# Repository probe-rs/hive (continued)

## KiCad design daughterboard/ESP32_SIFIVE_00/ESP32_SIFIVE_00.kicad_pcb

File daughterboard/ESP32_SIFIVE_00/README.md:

## Daughterboard ESP32_SIFIVE_00
This board features RISC-V and Xtensa cores.

### Targets
The following targets are implemented on this Daughterboard:
| Designation | MCU |
| --- | --- |
| target0 | ESP32-S3-WROOM-1-N8R8 |
| target1 | ESP32-S2 |
| target2 | LOFIVE-R1 (FE310-G002) |
| target3 | ESP32-C3 |

### Partlist
The partlist for this Daughterboard is available [here](https://octopart.com/bom-tool/JTwGMmL3).

### Other
The target3 and target1 devices have separate flash memory, as the currently available cores do not have any embedded flash.

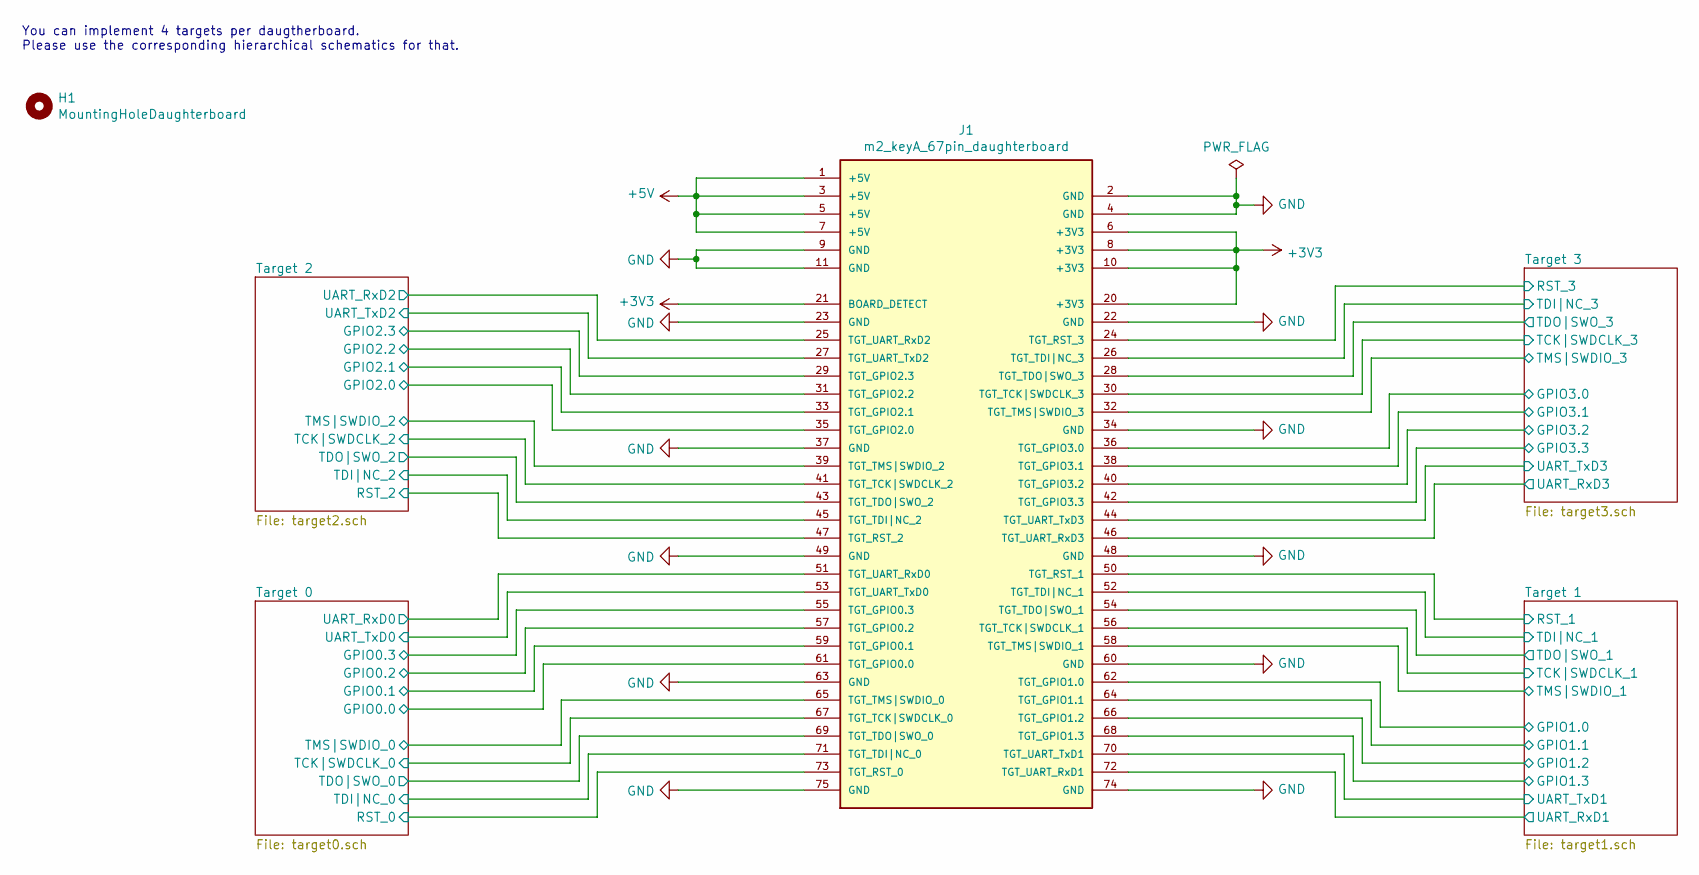
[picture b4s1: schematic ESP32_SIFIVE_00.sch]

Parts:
H1: MountingHoleDaughterboard; MountingHole_2.7mm_M2.5
J1: m2_keyA_67pin_daughterboard; m2_keyB

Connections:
+3V3: J1.6 (+3V3), J1.8 (+3V3), J1.10 (+3V3), J1.20 (+3V3), J1.21 (BOARD_DETECT); also elsewhere on the board
+5V: J1.1 (+5V), J1.3 (+5V), J1.5 (+5V), J1.7 (+5V); also elsewhere on the board
/Target 0/GPIO0.0: J1.61 (TGT_GPIO0.0); also elsewhere on the board
/Target 0/GPIO0.1: J1.59 (TGT_GPIO0.1); also elsewhere on the board
/Target 0/GPIO0.2: J1.57 (TGT_GPIO0.2); also elsewhere on the board
/Target 0/GPIO0.3: J1.55 (TGT_GPIO0.3); also elsewhere on the board
/Target 0/RST_0: J1.73 (TGT_RST_0); also elsewhere on the board
/Target 0/TCK|SWDCLK_0: J1.67 (TGT_TCK|SWDCLK_0); also elsewhere on the board
/Target 0/TDI|NC_0: J1.71 (TGT_TDI|NC_0); also elsewhere on the board
/Target 0/TDO|SWO_0: J1.69 (TGT_TDO|SWO_0); also elsewhere on the board
/Target 0/TMS|SWDIO_0: J1.65 (TGT_TMS|SWDIO_0); also elsewhere on the board
/Target 0/UART_RxD0: J1.51 (TGT_UART_RxD0); also elsewhere on the board
/Target 0/UART_TxD0: J1.53 (TGT_UART_TxD0); also elsewhere on the board
/Target 1/GPIO1.0: J1.62 (TGT_GPIO1.0); also elsewhere on the board
/Target 1/GPIO1.1: J1.64 (TGT_GPIO1.1); also elsewhere on the board
/Target 1/GPIO1.2: J1.66 (TGT_GPIO1.2); also elsewhere on the board
/Target 1/GPIO1.3: J1.68 (TGT_GPIO1.3); also elsewhere on the board
/Target 1/RST_1: J1.50 (TGT_RST_1); also elsewhere on the board
/Target 1/TCK|SWDCLK_1: J1.56 (TGT_TCK|SWDCLK_1); also elsewhere on the board
/Target 1/TDI|NC_1: J1.52 (TGT_TDI|NC_1); also elsewhere on the board
/Target 1/TDO|SWO_1: J1.54 (TGT_TDO|SWO_1); also elsewhere on the board
/Target 1/TMS|SWDIO_1: J1.58 (TGT_TMS|SWDIO_1); also elsewhere on the board
/Target 1/UART_RxD1: J1.72 (TGT_UART_RxD1); also elsewhere on the board
/Target 1/UART_TxD1: J1.70 (TGT_UART_TxD1); also elsewhere on the board
/Target 2/GPIO2.0: J1.35 (TGT_GPIO2.0); also elsewhere on the board
/Target 2/GPIO2.1: J1.33 (TGT_GPIO2.1); also elsewhere on the board
/Target 2/GPIO2.2: J1.31 (TGT_GPIO2.2); also elsewhere on the board
/Target 2/GPIO2.3: J1.29 (TGT_GPIO2.3); also elsewhere on the board
/Target 2/RST_2: J1.47 (TGT_RST_2); also elsewhere on the board
/Target 2/TCK|SWDCLK_2: J1.41 (TGT_TCK|SWDCLK_2); also elsewhere on the board
/Target 2/TDI|NC_2: J1.45 (TGT_TDI|NC_2); also elsewhere on the board
/Target 2/TDO|SWO_2: J1.43 (TGT_TDO|SWO_2); also elsewhere on the board
/Target 2/TMS|SWDIO_2: J1.39 (TGT_TMS|SWDIO_2); also elsewhere on the board
/Target 2/UART_RxD2: J1.25 (TGT_UART_RxD2); also elsewhere on the board
/Target 2/UART_TxD2: J1.27 (TGT_UART_TxD2); also elsewhere on the board
/Target 3/GPIO3.0: J1.36 (TGT_GPIO3.0); also elsewhere on the board
/Target 3/GPIO3.1: J1.38 (TGT_GPIO3.1); also elsewhere on the board
/Target 3/GPIO3.2: J1.40 (TGT_GPIO3.2); also elsewhere on the board
/Target 3/GPIO3.3: J1.42 (TGT_GPIO3.3); also elsewhere on the board
/Target 3/RST_3: J1.24 (TGT_RST_3); also elsewhere on the board
/Target 3/TCK|SWDCLK_3: J1.30 (TGT_TCK|SWDCLK_3); also elsewhere on the board
/Target 3/TDI|NC_3: J1.26 (TGT_TDI|NC_3); also elsewhere on the board
/Target 3/TDO|SWO_3: J1.28 (TGT_TDO|SWO_3); also elsewhere on the board
/Target 3/TMS|SWDIO_3: J1.32 (TGT_TMS|SWDIO_3); also elsewhere on the board
/Target 3/UART_RxD3: J1.46 (TGT_UART_RxD3); also elsewhere on the board
/Target 3/UART_TxD3: J1.44 (TGT_UART_TxD3); also elsewhere on the board
GND: J1.2 (GND), J1.4 (GND), J1.9 (GND), J1.11 (GND), J1.22 (GND), J1.23 (GND), J1.34 (GND), J1.37 (GND), J1.48 (GND), J1.49 (GND), J1.60 (GND), J1.63 (GND), J1.74 (GND), J1.75 (GND); also elsewhere on the board

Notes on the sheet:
You can implement 4 targets per daugtherboard. Please use the corresponding hierarchical schematics for that.

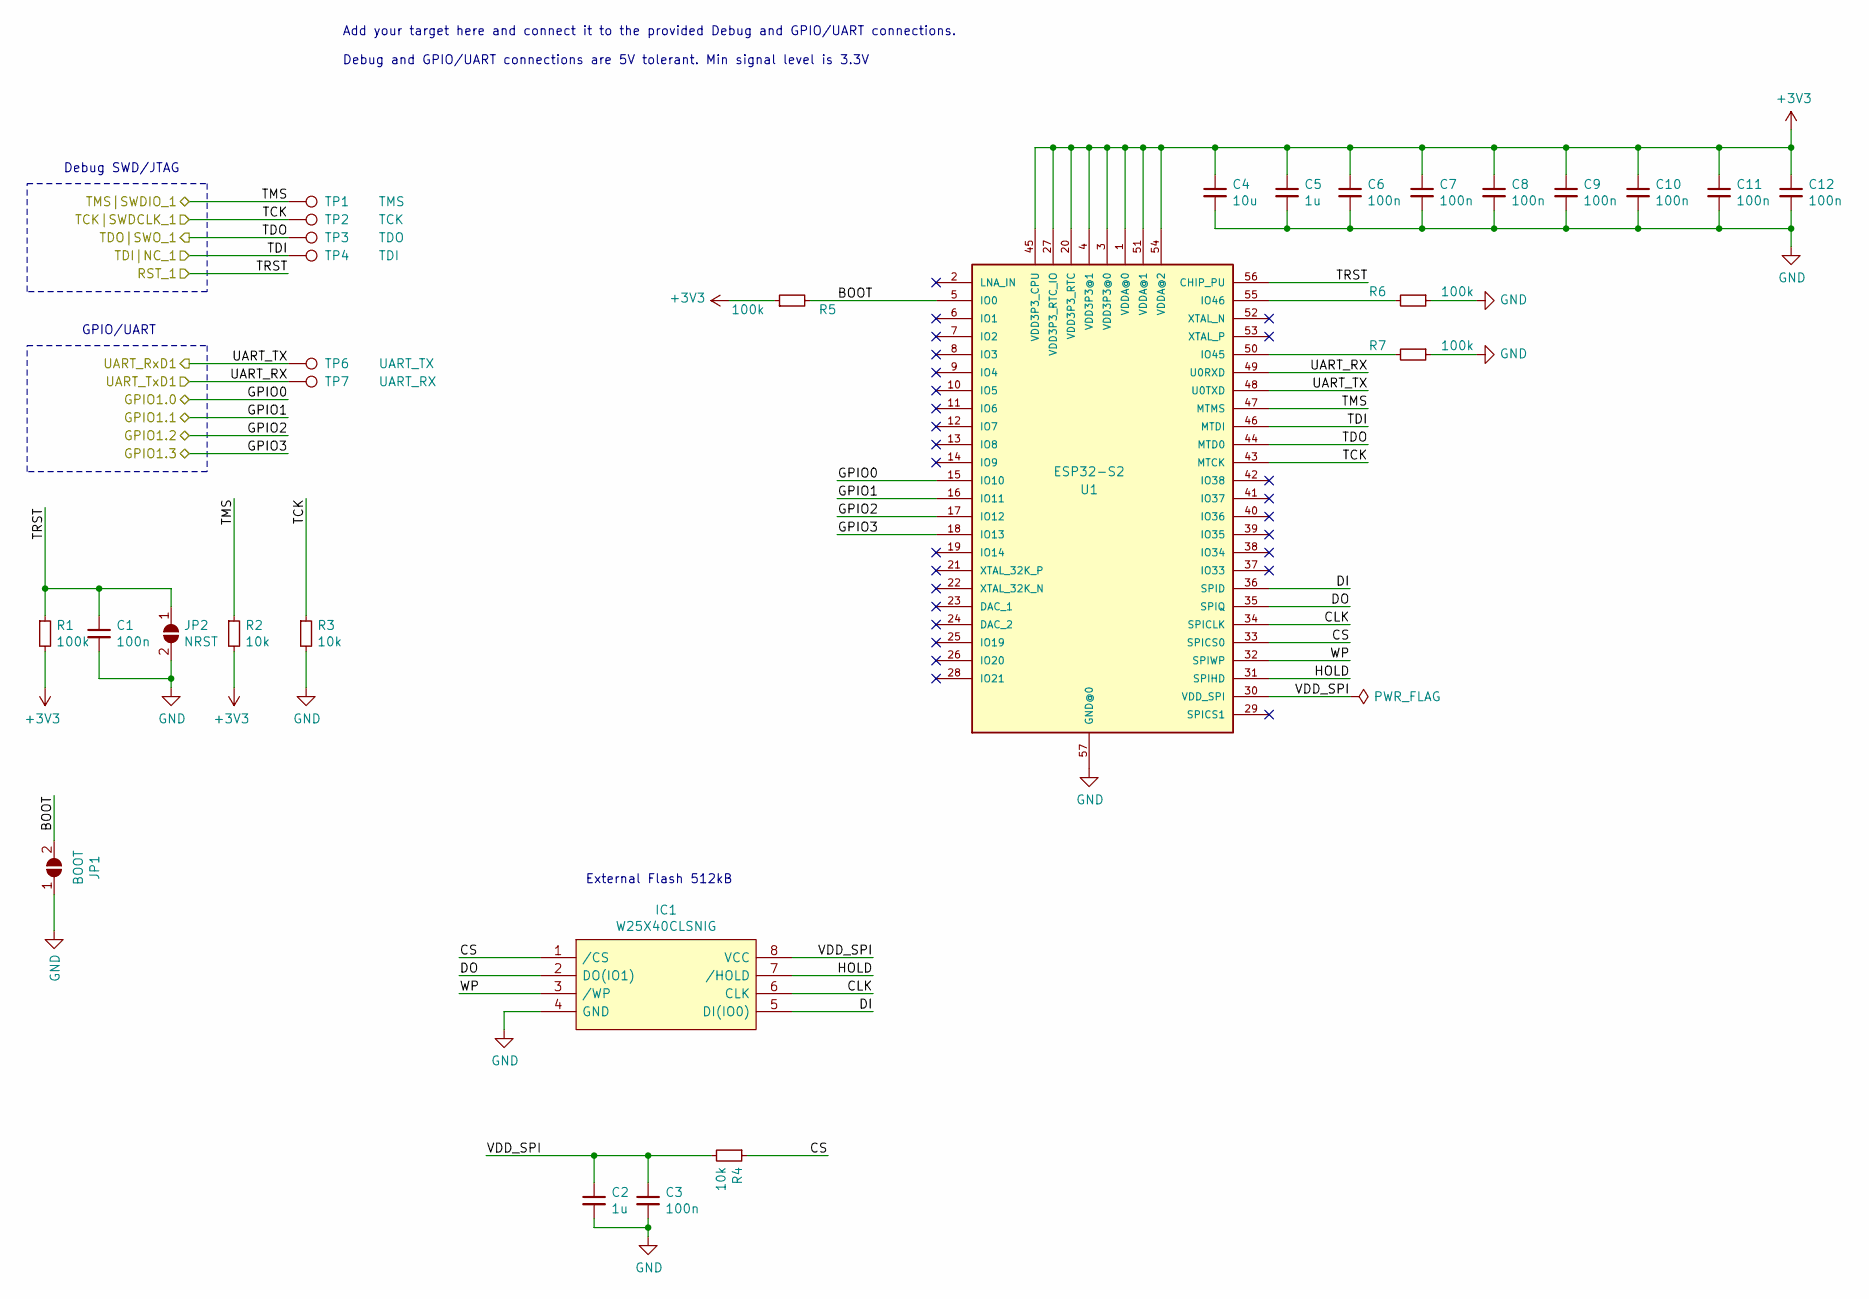
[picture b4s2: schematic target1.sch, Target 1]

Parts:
C1, C3, C6, C7, C8, C9, C10, C11, C12: 100n; C_0603_1608Metric_Pad1.05x0.95mm_HandSolder
C2, C5: 1u; C_0603_1608Metric_Pad1.05x0.95mm_HandSolder
C4: 10u; C_0603_1608Metric_Pad1.05x0.95mm_HandSolder
IC1: W25X40CLSNIG; Mouser Part Number 454-W25X40CLSNIG
JP1: BOOT; SolderJumper-2_P1.3mm_Open_TrianglePad1.0x1.5mm
JP2: NRST; SolderJumper-2_P1.3mm_Open_TrianglePad1.0x1.5mm
R1, R5, R6, R7: 100k; R_0603_1608Metric_Pad1.05x0.95mm_HandSolder
R2, R3, R4: 10k; R_0603_1608Metric_Pad1.05x0.95mm_HandSolder
TP1: TMS; TestPoint_Pad_1.0x1.0mm
TP2: TCK; TestPoint_Pad_1.0x1.0mm
TP3: TDO; TestPoint_Pad_1.0x1.0mm
TP4: TDI; TestPoint_Pad_1.0x1.0mm
TP6: UART_TX; TestPoint_Pad_1.0x1.0mm
TP7: UART_RX; TestPoint_Pad_1.0x1.0mm
U1: ESP32-S2; MANUFACTURER_PART_NUMBE ESP32-S2

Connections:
+3V3: C4.1, C5.1, C6.1, C7.1, C8.1, C9.1, C10.1, C11.1, C12.1, R1.2, R2.2, R5.1, U1.1 (VDDA@0), U1.3 (VDD3P3@0), U1.4 (VDD3P3@1), U1.20 (VDD3P3_RTC), U1.27 (VDD3P3_RTC_IO), U1.45 (VDD3P3_CPU), U1.51 (VDDA@1), U1.54 (VDDA@2); also elsewhere on the board
/Target 1/BOOT: JP1.2 (B), R5.2, U1.5 (IO0)
/Target 1/CLK: IC1.6 (CLK), U1.34 (SPICLK)
/Target 1/CS: IC1.1 (/CS), R4.1, U1.33 (SPICS0)
/Target 1/DI: IC1.5 (DI(IO0)), U1.36 (SPID)
/Target 1/DO: IC1.2 (DO(IO1)), U1.35 (SPIQ)
/Target 1/GPIO1.0: U1.15 (IO10); also elsewhere on the board
/Target 1/GPIO1.1: U1.16 (IO11); also elsewhere on the board
/Target 1/GPIO1.2: U1.17 (IO12); also elsewhere on the board
/Target 1/GPIO1.3: U1.18 (IO13); also elsewhere on the board
/Target 1/HOLD: IC1.7 (/HOLD), U1.31 (SPIHD)
/Target 1/RST_1: C1.1, JP2.1 (A), R1.1, U1.56 (CHIP_PU); also elsewhere on the board
/Target 1/TCK|SWDCLK_1: R3.1, TP2.1, U1.43 (MTCK); also elsewhere on the board
/Target 1/TDI|NC_1: TP4.1, U1.46 (MTDI); also elsewhere on the board
/Target 1/TDO|SWO_1: TP3.1, U1.44 (MTD0); also elsewhere on the board
/Target 1/TMS|SWDIO_1: R2.1, TP1.1, U1.47 (MTMS); also elsewhere on the board
/Target 1/UART_RxD1: TP6.1, U1.48 (U0TXD); also elsewhere on the board
/Target 1/UART_TxD1: TP7.1, U1.49 (U0RXD); also elsewhere on the board
/Target 1/VDD_SPI: C2.1, C3.1, IC1.8 (VCC), R4.2, U1.30 (VDD_SPI)
/Target 1/WP: IC1.3 (/WP), U1.32 (SPIWP)
GND: C1.2, C2.2, C3.2, C4.2, C5.2, C6.2, C7.2, C8.2, C9.2, C10.2, C11.2, C12.2, IC1.4 (GND), JP1.1 (A), JP2.2 (B), R3.2, R6.1, R7.1, U1.57 (GND@0); also elsewhere on the board
unnamed: R6.2, U1.55 (IO46)
unnamed: R7.2, U1.50 (IO45)

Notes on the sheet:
Debug SWD/JTAG
GPIO/UART
Add your target here and connect it to the provided Debug and GPIO/UART connections. Debug and GPIO/UART connections are 5V tolerant. Min signal level is 3.3V
External Flash 512kB

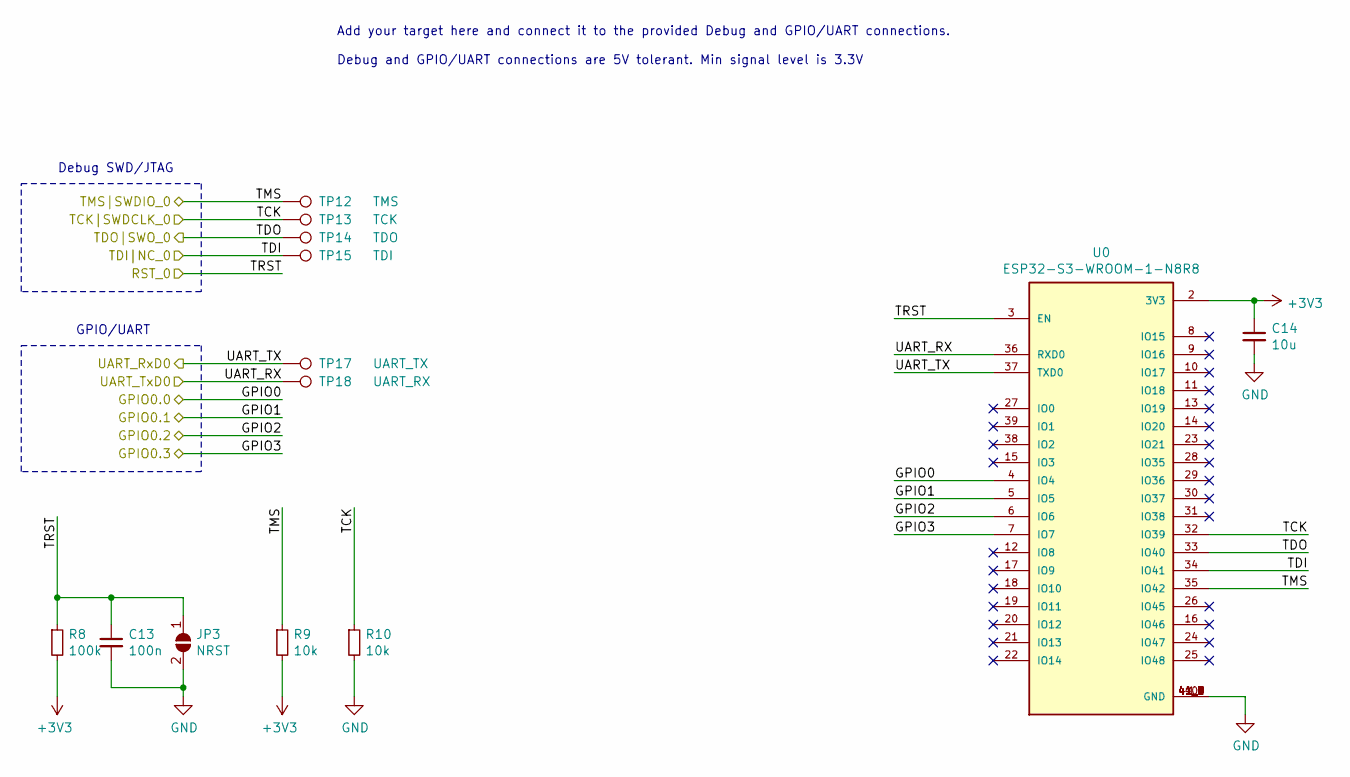
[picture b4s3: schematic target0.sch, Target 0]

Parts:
C13: 100n; C_0603_1608Metric_Pad1.05x0.95mm_HandSolder
C14: 10u; C_0603_1608Metric_Pad1.05x0.95mm_HandSolder
JP3: NRST; SolderJumper-2_P1.3mm_Open_TrianglePad1.0x1.5mm
R8: 100k; R_0603_1608Metric_Pad1.05x0.95mm_HandSolder
R9, R10: 10k; R_0603_1608Metric_Pad1.05x0.95mm_HandSolder
TP12: TMS; TestPoint_Pad_1.0x1.0mm
TP13: TCK; TestPoint_Pad_1.0x1.0mm
TP14: TDO; TestPoint_Pad_1.0x1.0mm
TP15: TDI; TestPoint_Pad_1.0x1.0mm
TP17: UART_TX; TestPoint_Pad_1.0x1.0mm
TP18: UART_RX; TestPoint_Pad_1.0x1.0mm
U0: ESP32-S3-WROOM-1-N8R8; XCVR_ESP32-S3-WROOM-1-N8R8; PARTREV v0.6

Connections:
+3V3: C14.1, R8.2, R9.2, U0.2 (3V3); also elsewhere on the board
/Target 0/GPIO0.0: U0.4 (IO4); also elsewhere on the board
/Target 0/GPIO0.1: U0.5 (IO5); also elsewhere on the board
/Target 0/GPIO0.2: U0.6 (IO6); also elsewhere on the board
/Target 0/GPIO0.3: U0.7 (IO7); also elsewhere on the board
/Target 0/RST_0: C13.1, JP3.1 (A), R8.1, U0.3 (EN); also elsewhere on the board
/Target 0/TCK|SWDCLK_0: R10.1, TP13.1, U0.32 (IO39); also elsewhere on the board
/Target 0/TDI|NC_0: TP15.1, U0.34 (IO41); also elsewhere on the board
/Target 0/TDO|SWO_0: TP14.1, U0.33 (IO40); also elsewhere on the board
/Target 0/TMS|SWDIO_0: R9.1, TP12.1, U0.35 (IO42); also elsewhere on the board
/Target 0/UART_RxD0: TP17.1, U0.37 (TXD0); also elsewhere on the board
/Target 0/UART_TxD0: TP18.1, U0.36 (RXD0); also elsewhere on the board
GND: C13.2, C14.2, JP3.2 (B), R10.2, U0.1 (GND), U0.40 (GND), U0.41_1 (GND), U0.41_2 (GND), U0.41_3 (GND), U0.41_4 (GND), U0.41_5 (GND), U0.41_6 (GND), U0.41_7 (GND), U0.41_8 (GND), U0.41_9 (GND); also elsewhere on the board

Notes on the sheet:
Debug SWD/JTAG
GPIO/UART
Add your target here and connect it to the provided Debug and GPIO/UART connections. Debug and GPIO/UART connections are 5V tolerant. Min signal level is 3.3V

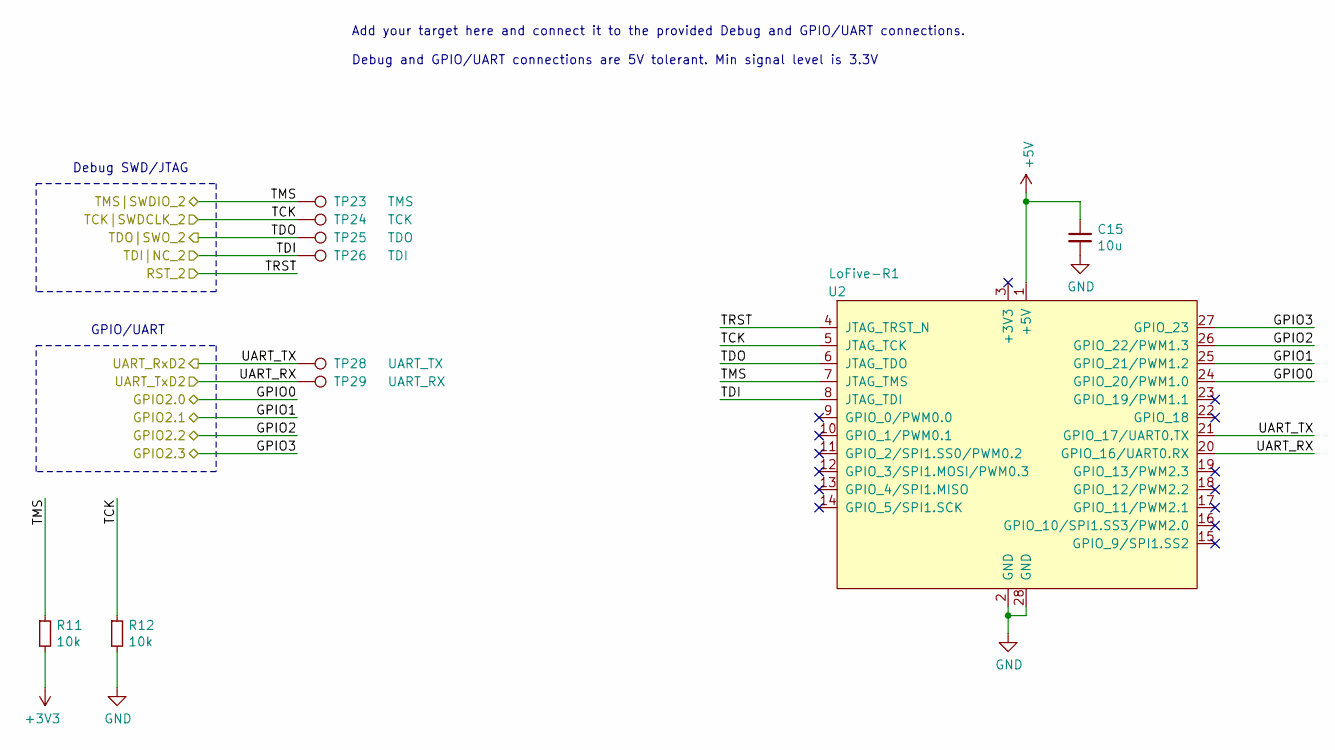
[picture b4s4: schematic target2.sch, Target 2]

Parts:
C15: 10u; C_0603_1608Metric_Pad1.05x0.95mm_HandSolder
R11, R12: 10k; R_0603_1608Metric_Pad1.05x0.95mm_HandSolder
TP23: TMS; TestPoint_Pad_1.0x1.0mm
TP24: TCK; TestPoint_Pad_1.0x1.0mm
TP25: TDO; TestPoint_Pad_1.0x1.0mm
TP26: TDI; TestPoint_Pad_1.0x1.0mm
TP28: UART_TX; TestPoint_Pad_1.0x1.0mm
TP29: UART_RX; TestPoint_Pad_1.0x1.0mm
U2: LoFive-R1

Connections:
+3V3: R11.2; also elsewhere on the board
+5V: C15.1, U2.1 (+5V); also elsewhere on the board
/Target 2/GPIO2.0: U2.24 (GPIO_20/PWM1.0); also elsewhere on the board
/Target 2/GPIO2.1: U2.25 (GPIO_21/PWM1.2); also elsewhere on the board
/Target 2/GPIO2.2: U2.26 (GPIO_22/PWM1.3); also elsewhere on the board
/Target 2/GPIO2.3: U2.27 (GPIO_23); also elsewhere on the board
/Target 2/RST_2: U2.4 (JTAG_TRST_N); also elsewhere on the board
/Target 2/TCK|SWDCLK_2: R12.1, TP24.1, U2.5 (JTAG_TCK); also elsewhere on the board
/Target 2/TDI|NC_2: TP26.1, U2.8 (JTAG_TDI); also elsewhere on the board
/Target 2/TDO|SWO_2: TP25.1, U2.6 (JTAG_TDO); also elsewhere on the board
/Target 2/TMS|SWDIO_2: R11.1, TP23.1, U2.7 (JTAG_TMS); also elsewhere on the board
/Target 2/UART_RxD2: TP28.1, U2.21 (GPIO_17/UART0.TX); also elsewhere on the board
/Target 2/UART_TxD2: TP29.1, U2.20 (GPIO_16/UART0.RX); also elsewhere on the board
GND: C15.2, R12.2, U2.2 (GND), U2.28 (GND); also elsewhere on the board

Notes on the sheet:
Debug SWD/JTAG
GPIO/UART
Add your target here and connect it to the provided Debug and GPIO/UART connections. Debug and GPIO/UART connections are 5V tolerant. Min signal level is 3.3V

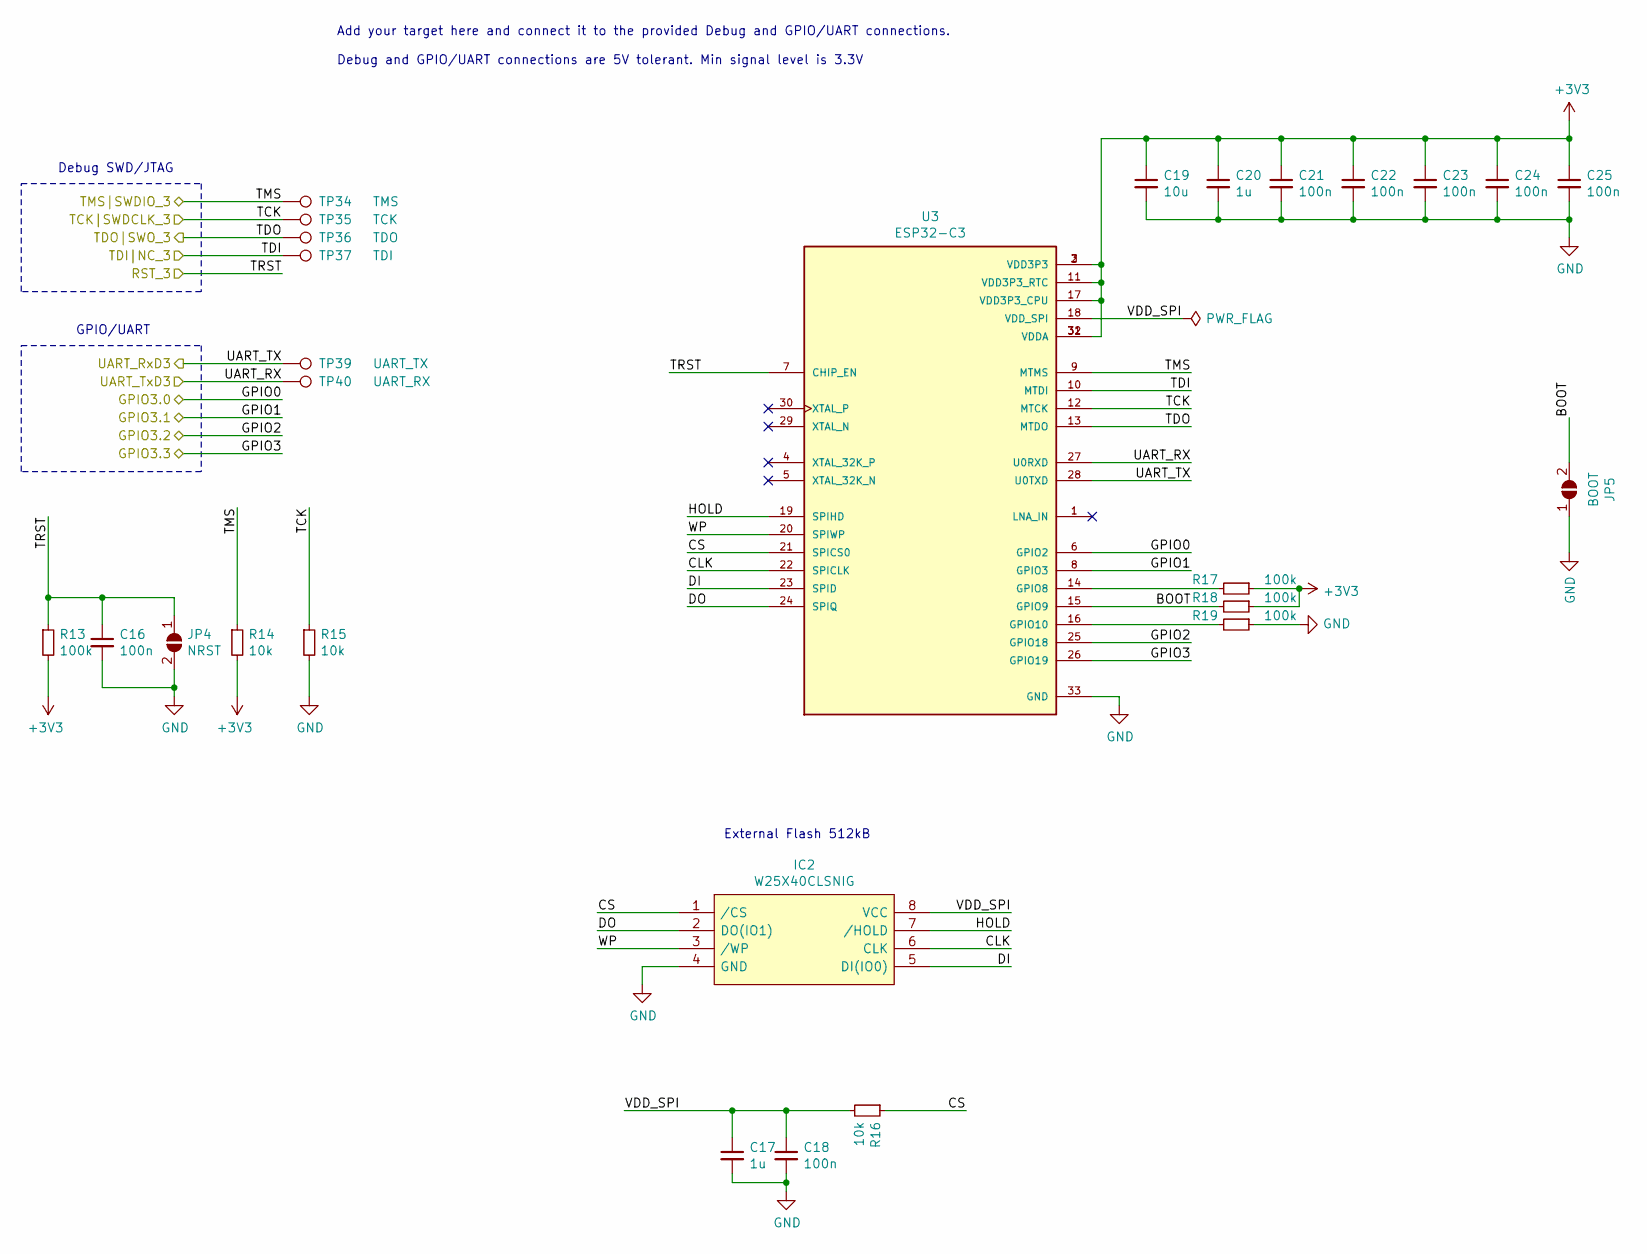
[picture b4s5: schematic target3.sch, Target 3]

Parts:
C16, C18, C21, C22, C23, C24, C25: 100n; C_0603_1608Metric_Pad1.05x0.95mm_HandSolder
C17, C20: 1u; C_0603_1608Metric_Pad1.05x0.95mm_HandSolder
C19: 10u; C_0603_1608Metric_Pad1.05x0.95mm_HandSolder
IC2: W25X40CLSNIG; Mouser Part Number 454-W25X40CLSNIG
JP4: NRST; SolderJumper-2_P1.3mm_Open_TrianglePad1.0x1.5mm
JP5: BOOT; SolderJumper-2_P1.3mm_Open_TrianglePad1.0x1.5mm
R13, R17, R18, R19: 100k; R_0603_1608Metric_Pad1.05x0.95mm_HandSolder
R14, R15, R16: 10k; R_0603_1608Metric_Pad1.05x0.95mm_HandSolder
TP34: TMS; TestPoint_Pad_1.0x1.0mm
TP35: TCK; TestPoint_Pad_1.0x1.0mm
TP36: TDO; TestPoint_Pad_1.0x1.0mm
TP37: TDI; TestPoint_Pad_1.0x1.0mm
TP39: UART_TX; TestPoint_Pad_1.0x1.0mm
TP40: UART_RX; TestPoint_Pad_1.0x1.0mm
U3: ESP32-C3; PARTREV V1.0

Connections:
+3V3: C19.1, C20.1, C21.1, C22.1, C23.1, C24.1, C25.1, R13.2, R14.2, R17.1, R18.1, U3.2 (VDD3P3), U3.3 (VDD3P3), U3.11 (VDD3P3_RTC), U3.17 (VDD3P3_CPU), U3.31 (VDDA), U3.32 (VDDA); also elsewhere on the board
/Target 3/BOOT: JP5.2 (B), R18.2, U3.15 (GPIO9)
/Target 3/CLK: IC2.6 (CLK), U3.22 (SPICLK)
/Target 3/CS: IC2.1 (/CS), R16.1, U3.21 (SPICS0)
/Target 3/DI: IC2.5 (DI(IO0)), U3.23 (SPID)
/Target 3/DO: IC2.2 (DO(IO1)), U3.24 (SPIQ)
/Target 3/GPIO3.0: U3.6 (GPIO2); also elsewhere on the board
/Target 3/GPIO3.1: U3.8 (GPIO3); also elsewhere on the board
/Target 3/GPIO3.2: U3.25 (GPIO18); also elsewhere on the board
/Target 3/GPIO3.3: U3.26 (GPIO19); also elsewhere on the board
/Target 3/HOLD: IC2.7 (/HOLD), U3.19 (SPIHD)
/Target 3/RST_3: C16.1, JP4.1 (A), R13.1, U3.7 (CHIP_EN); also elsewhere on the board
/Target 3/TCK|SWDCLK_3: R15.1, TP35.1, U3.12 (MTCK); also elsewhere on the board
/Target 3/TDI|NC_3: TP37.1, U3.10 (MTDI); also elsewhere on the board
/Target 3/TDO|SWO_3: TP36.1, U3.13 (MTDO); also elsewhere on the board
/Target 3/TMS|SWDIO_3: R14.1, TP34.1, U3.9 (MTMS); also elsewhere on the board
/Target 3/UART_RxD3: TP39.1, U3.28 (U0TXD); also elsewhere on the board
/Target 3/UART_TxD3: TP40.1, U3.27 (U0RXD); also elsewhere on the board
/Target 3/VDD_SPI: C17.1, C18.1, IC2.8 (VCC), R16.2, U3.18 (VDD_SPI)
/Target 3/WP: IC2.3 (/WP), U3.20 (SPIWP)
GND: C16.2, C17.2, C18.2, C19.2, C20.2, C21.2, C22.2, C23.2, C24.2, C25.2, IC2.4 (GND), JP4.2 (B), JP5.1 (A), R15.2, R19.1, U3.33 (GND); also elsewhere on the board
unnamed: R17.2, U3.14 (GPIO8)
unnamed: R19.2, U3.16 (GPIO10)

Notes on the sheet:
Debug SWD/JTAG
GPIO/UART
Add your target here and connect it to the provided Debug and GPIO/UART connections. Debug and GPIO/UART connections are 5V tolerant. Min signal level is 3.3V
External Flash 512kB

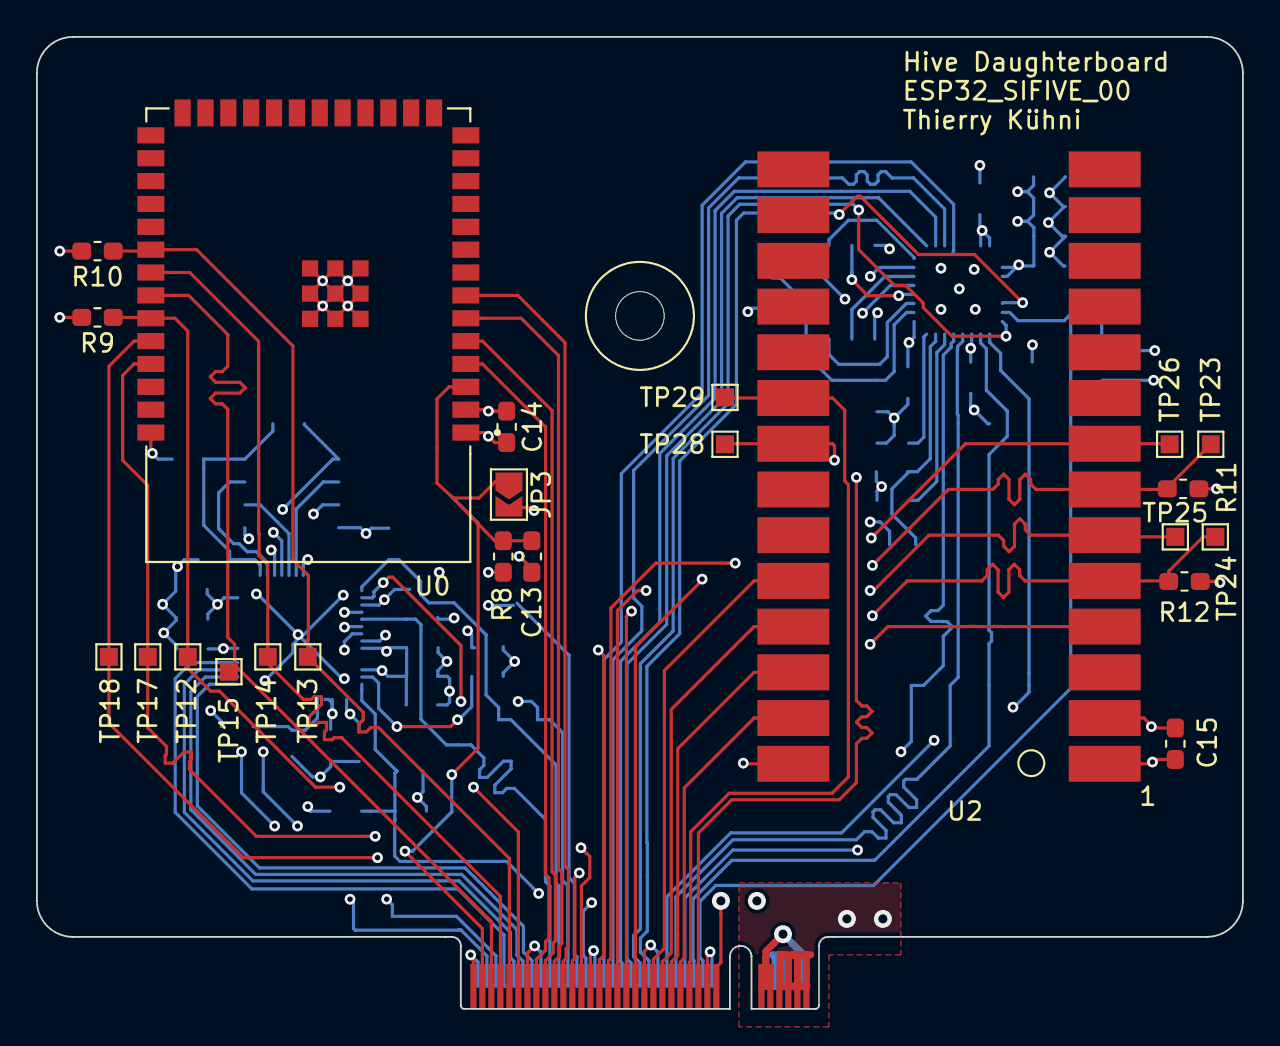
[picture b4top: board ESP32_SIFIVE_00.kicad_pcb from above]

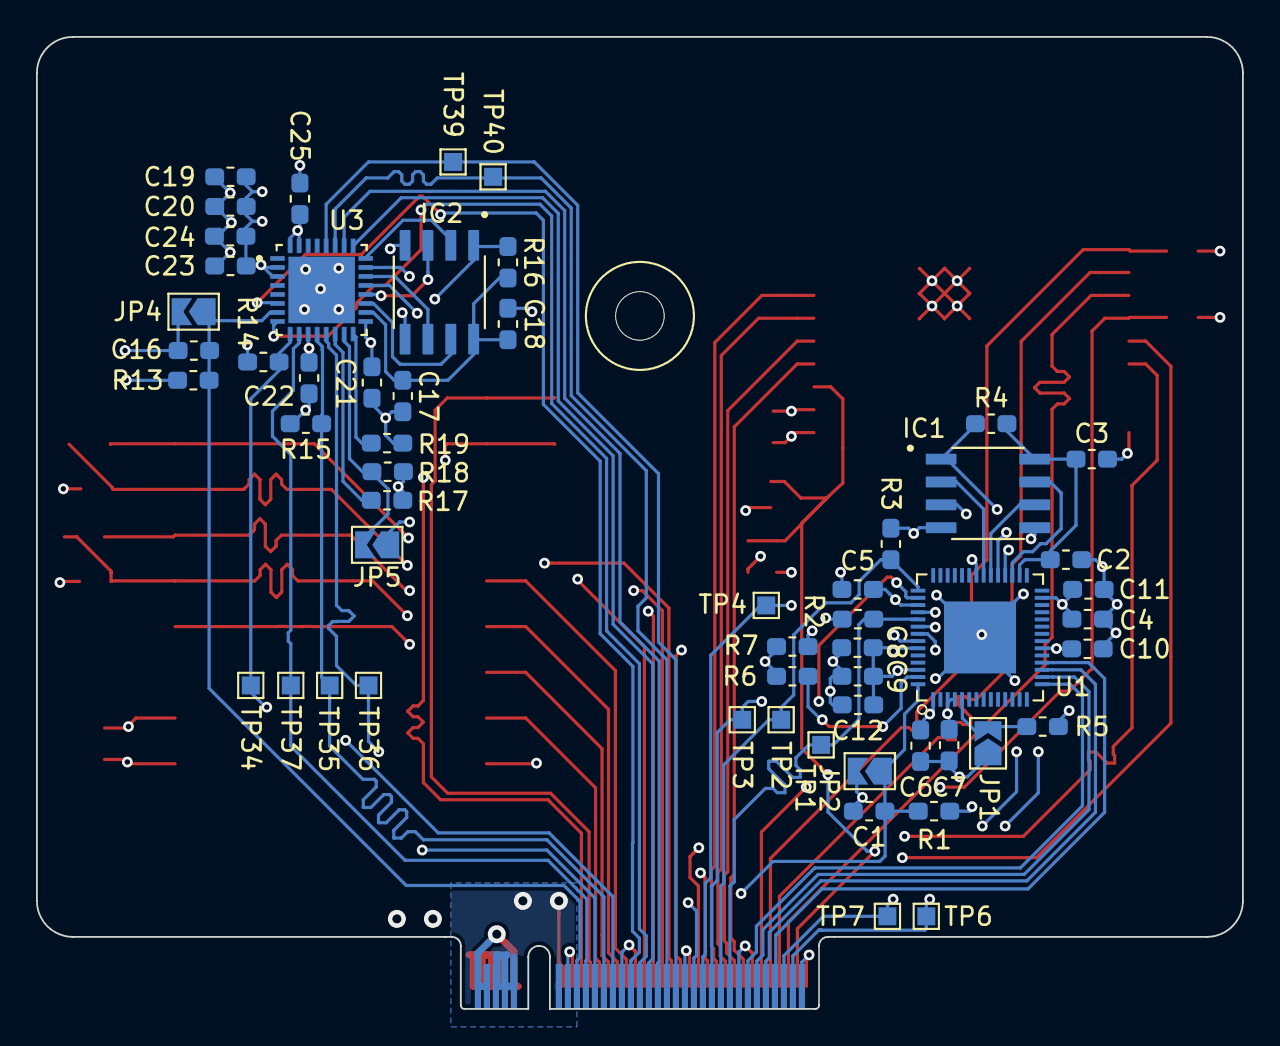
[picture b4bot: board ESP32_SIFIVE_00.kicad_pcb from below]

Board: 4 copper layers, 67.0 x 54.0 mm, 81 parts (56 on the bottom side), 67 nets.

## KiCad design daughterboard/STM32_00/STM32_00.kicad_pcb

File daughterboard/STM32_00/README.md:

## Daughterboard STM32_00
This Daughterboard features several STM32 MCUs.

### Targets
The following targets are implemented on this Daughterboard:
| Designation | MCU |
| --- | --- |
| target0 | STM32G031F4P6 |
| target1 | STM32F401CCU6 |
| target2 | STM32L151C8T6A |
| target3 | STM32F103C8T6 |

### Partlist
The partlist for this Daughterboard is available [here](https://octopart.com/bom-tool/za3WrhSx).

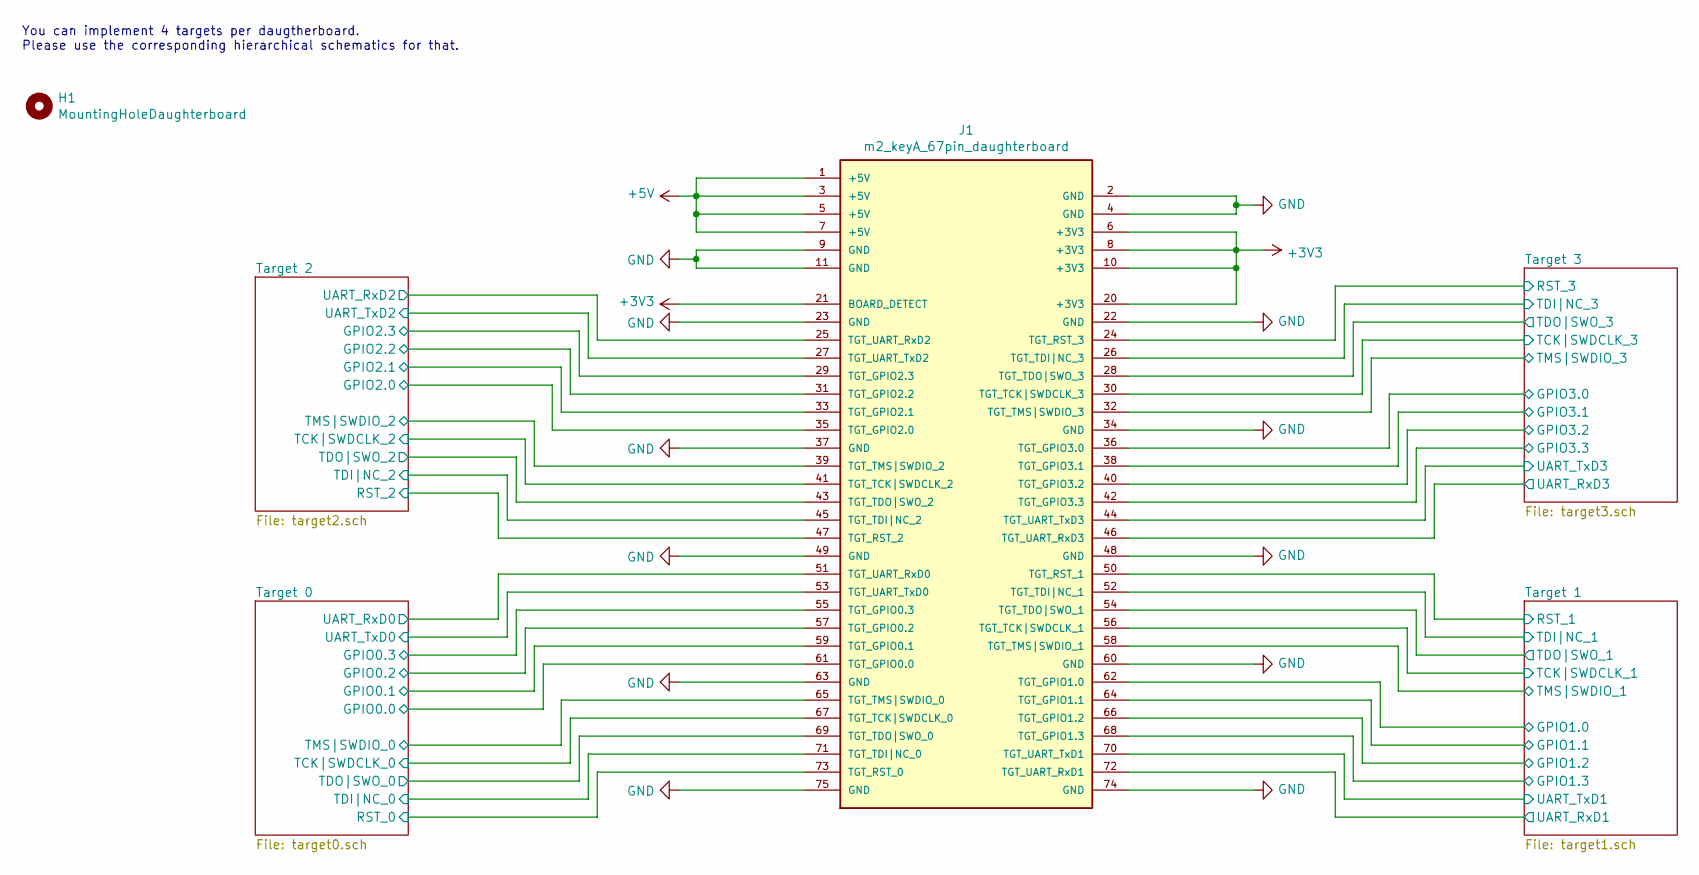
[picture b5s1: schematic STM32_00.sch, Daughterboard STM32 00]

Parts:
H1: MountingHoleDaughterboard; MountingHole_2.7mm_M2.5
J1: m2_keyA_67pin_daughterboard; m2_keyB

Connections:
+3V3: J1.6 (+3V3), J1.8 (+3V3), J1.10 (+3V3), J1.20 (+3V3), J1.21 (BOARD_DETECT); also elsewhere on the board
+5V: J1.1 (+5V), J1.3 (+5V), J1.5 (+5V), J1.7 (+5V)
/Target 0/GPIO0.0: J1.61 (TGT_GPIO0.0); also elsewhere on the board
/Target 0/GPIO0.1: J1.59 (TGT_GPIO0.1); also elsewhere on the board
/Target 0/GPIO0.2: J1.57 (TGT_GPIO0.2); also elsewhere on the board
/Target 0/GPIO0.3: J1.55 (TGT_GPIO0.3); also elsewhere on the board
/Target 0/RST_0: J1.73 (TGT_RST_0); also elsewhere on the board
/Target 0/TCK|SWDCLK_0: J1.67 (TGT_TCK|SWDCLK_0); also elsewhere on the board
/Target 0/TDI|NC_0: J1.71 (TGT_TDI|NC_0); also elsewhere on the board
/Target 0/TDO|SWO_0: J1.69 (TGT_TDO|SWO_0); also elsewhere on the board
/Target 0/TMS|SWDIO_0: J1.65 (TGT_TMS|SWDIO_0); also elsewhere on the board
/Target 0/UART_RxD0: J1.51 (TGT_UART_RxD0); also elsewhere on the board
/Target 0/UART_TxD0: J1.53 (TGT_UART_TxD0); also elsewhere on the board
/Target 1/GPIO1.0: J1.62 (TGT_GPIO1.0); also elsewhere on the board
/Target 1/GPIO1.1: J1.64 (TGT_GPIO1.1); also elsewhere on the board
/Target 1/GPIO1.2: J1.66 (TGT_GPIO1.2); also elsewhere on the board
/Target 1/GPIO1.3: J1.68 (TGT_GPIO1.3); also elsewhere on the board
/Target 1/RST_1: J1.50 (TGT_RST_1); also elsewhere on the board
/Target 1/TCK|SWDCLK_1: J1.56 (TGT_TCK|SWDCLK_1); also elsewhere on the board
/Target 1/TDI|NC_1: J1.52 (TGT_TDI|NC_1); also elsewhere on the board
/Target 1/TDO|SWO_1: J1.54 (TGT_TDO|SWO_1); also elsewhere on the board
/Target 1/TMS|SWDIO_1: J1.58 (TGT_TMS|SWDIO_1); also elsewhere on the board
/Target 1/UART_RxD1: J1.72 (TGT_UART_RxD1); also elsewhere on the board
/Target 1/UART_TxD1: J1.70 (TGT_UART_TxD1); also elsewhere on the board
/Target 2/GPIO2.0: J1.35 (TGT_GPIO2.0); also elsewhere on the board
/Target 2/GPIO2.1: J1.33 (TGT_GPIO2.1); also elsewhere on the board
/Target 2/GPIO2.2: J1.31 (TGT_GPIO2.2); also elsewhere on the board
/Target 2/GPIO2.3: J1.29 (TGT_GPIO2.3); also elsewhere on the board
/Target 2/RST_2: J1.47 (TGT_RST_2); also elsewhere on the board
/Target 2/TCK|SWDCLK_2: J1.41 (TGT_TCK|SWDCLK_2); also elsewhere on the board
/Target 2/TDI|NC_2: J1.45 (TGT_TDI|NC_2); also elsewhere on the board
/Target 2/TDO|SWO_2: J1.43 (TGT_TDO|SWO_2); also elsewhere on the board
/Target 2/TMS|SWDIO_2: J1.39 (TGT_TMS|SWDIO_2); also elsewhere on the board
/Target 2/UART_RxD2: J1.25 (TGT_UART_RxD2); also elsewhere on the board
/Target 2/UART_TxD2: J1.27 (TGT_UART_TxD2); also elsewhere on the board
/Target 3/GPIO3.0: J1.36 (TGT_GPIO3.0); also elsewhere on the board
/Target 3/GPIO3.1: J1.38 (TGT_GPIO3.1); also elsewhere on the board
/Target 3/GPIO3.2: J1.40 (TGT_GPIO3.2); also elsewhere on the board
/Target 3/GPIO3.3: J1.42 (TGT_GPIO3.3); also elsewhere on the board
/Target 3/RST_3: J1.24 (TGT_RST_3); also elsewhere on the board
/Target 3/TCK|SWDCLK_3: J1.30 (TGT_TCK|SWDCLK_3); also elsewhere on the board
/Target 3/TDI|NC_3: J1.26 (TGT_TDI|NC_3); also elsewhere on the board
/Target 3/TDO|SWO_3: J1.28 (TGT_TDO|SWO_3); also elsewhere on the board
/Target 3/TMS|SWDIO_3: J1.32 (TGT_TMS|SWDIO_3); also elsewhere on the board
/Target 3/UART_RxD3: J1.46 (TGT_UART_RxD3); also elsewhere on the board
/Target 3/UART_TxD3: J1.44 (TGT_UART_TxD3); also elsewhere on the board
GND: J1.2 (GND), J1.4 (GND), J1.9 (GND), J1.11 (GND), J1.22 (GND), J1.23 (GND), J1.34 (GND), J1.37 (GND), J1.48 (GND), J1.49 (GND), J1.60 (GND), J1.63 (GND), J1.74 (GND), J1.75 (GND); also elsewhere on the board

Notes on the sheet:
You can implement 4 targets per daugtherboard. Please use the corresponding hierarchical schematics for that.
